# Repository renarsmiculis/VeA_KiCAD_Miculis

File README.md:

# VeA_KiCAD_Miculis

This project is made for studies.

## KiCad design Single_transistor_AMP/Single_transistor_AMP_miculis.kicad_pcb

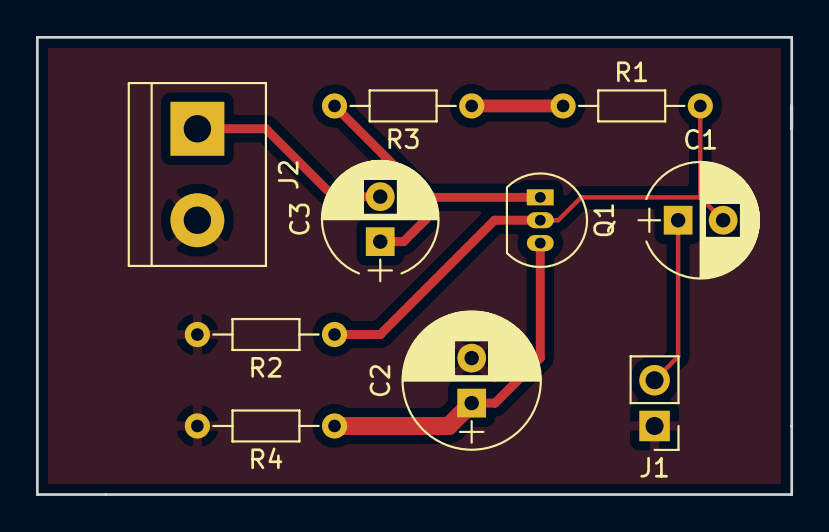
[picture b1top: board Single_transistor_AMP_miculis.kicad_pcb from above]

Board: 2 copper layers, 41.9 x 25.4 mm, 10 parts (0 on the bottom side), 7 nets.

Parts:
C1, C3: 20uF; CP_Radial_D6.3mm_P2.50mm
C2: 50uF; CP_Radial_D7.5mm_P2.50mm
J1: Conn_01x02; Pin_Header_Straight_1x02_Pitch2.54mm
J2: Conn_01x02; TerminalBlock_bornier-2_P5.08mm
Q1: BC548; TO-92_Inline_Narrow_Oval
R1: 22k; R_Axial_DIN0204_L3.6mm_D1.6mm_P7.62mm_Horizontal
R2: 6.8k; R_Axial_DIN0204_L3.6mm_D1.6mm_P7.62mm_Horizontal
R3: 4.7k; R_Axial_DIN0204_L3.6mm_D1.6mm_P7.62mm_Horizontal
R4: 1.8k; R_Axial_DIN0204_L3.6mm_D1.6mm_P7.62mm_Horizontal

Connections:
+12V: R1.1, R3.1
GND: C2.2, J1.1, J2.2, R2.2, R4.2
unnamed: C1.1, J1.2
unnamed: C1.2, Q1.2, R1.2, R2.1
unnamed: C2.1, Q1.3, R4.1
unnamed: C3.1, Q1.1, R3.2
unnamed: C3.2, J2.1

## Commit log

2018-02-22 README update to test GitHub Repo
2018-04-12 cloned
2018-04-12 cloned twice
2018-04-12 Deleted information
2018-04-12 MultiVib_homework
2018-04-26 SIngle_AMP
    SIngle_AMP
2018-06-10 Power supply
2018-06-12 Majas darbi
2018-06-13 Kursa darbs
2018-06-13 Kursa darba labojums
